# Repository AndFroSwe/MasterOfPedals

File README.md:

# Master of Pedals
A guitar pedal switching rig. Readymade presets are chosen by hitting a
footswitch on the stage pedal. The final goal of the repo is to have a modular
design that can easily be modified to the given specs.

# Features

1. At the hit of a footswitch, pedals are engaged as per the corresponding
   preset. No more tapdancing!
2. Presets can be changed on the main unit.

# Units

- __Control unit__: The main control unit. All pedals are connected to this and
presets are set here. 
- __Stage pedal__: Unit placed at the front of the stage. Has a set of
  footswitches for preset choice and a simple interface that shows the user
which preset is currently chosen.

# Repository guide

- __./Software/__ contains all source code for the MCUs. Divided into subfolders
  corresponding to the stage pedal and the control unit.
- __./KiCad/__ contains electrical schematics. Divided into subfolders
  corresponding to the stage pedal and the control unit.

# Prototype unit
The repo has a fully ready-to-go (when it's done) unit. This unit has the
following specs:

- 8 pedals in the control loop.
- 3 independently controlled amp channels.
- 6 presets.
- Stage pedal is connected via cord (i.e. it is not wireless).
- It has a simple user interface at the control unit that allows the user to
  change the presets.

# Future features
- __MIDI control output__: An output that can send MIDI messages to pedals.
- __Wireless control__: The stage pedal can send control signals to the control
  unit wirelessly. This also enables multiple control units. This could be used
in a mini control unit that is carried on the guitar.
- __Internal pedal power supply__: The control unit contains a PSU that can feed
  the guitar pedals with power.
- __Battery power supply__: The stage pedal runs on battery.
- __Data logging__: The pedal remembers which presets have been used.

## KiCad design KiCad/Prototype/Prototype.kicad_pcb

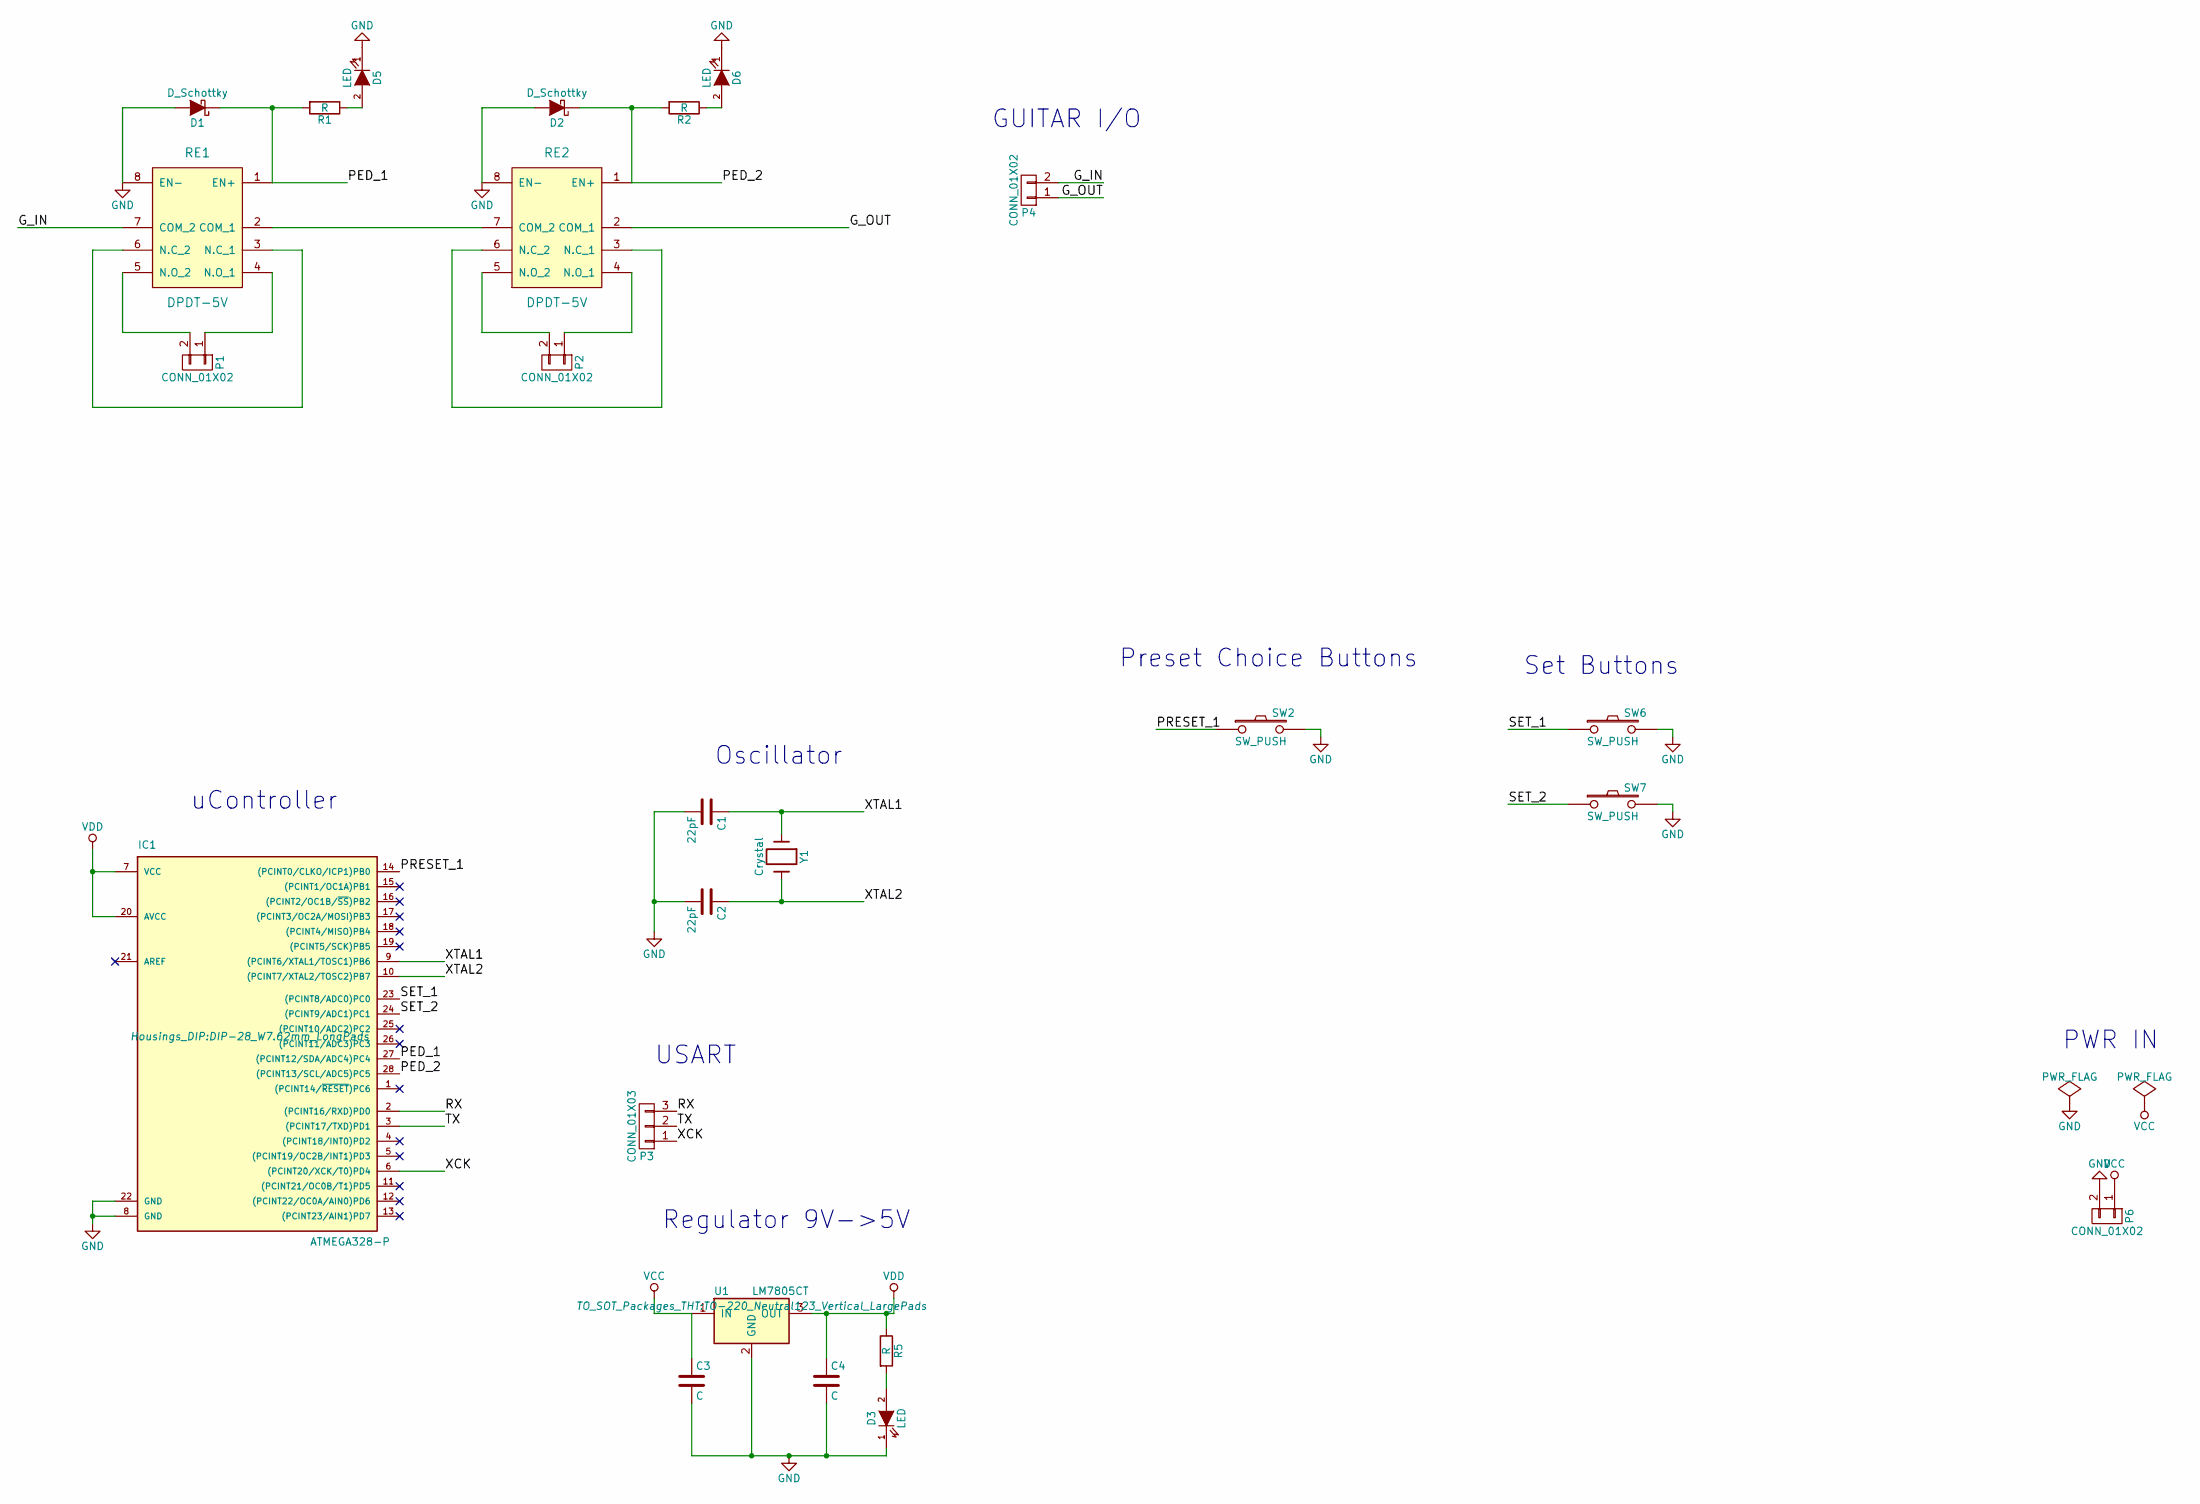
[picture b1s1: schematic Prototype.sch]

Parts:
C1, C2: 22pF; C_Disc_D3_P2.5
C3, C4: C; C_Rect_L7_W2_P5
D1, D2: D_Schottky; Diode_DO-41_SOD81_Vertical_AnodeUp
D3, D5, D6: LED; LED-5MM
IC1: ATMEGA328-P; DIP-28_W7.62mm_LongPads
P1, P2, P4, P6: CONN_01X02; Molex_KK-6410-02_02x2.54mm_Straight
P3: CONN_01X03; Molex_MicroLatch-53253-0370_03x2.00mm_Straight
R1, R2, R5: R; Resistor_Vertical_RM5mm
RE1, RE2: DPDT-5V; DS2Y_PAK
SW2, SW6, SW7: SW_PUSH; SW_PUSH_6mm
U1: LM7805CT; TO-220_Neutral123_Vertical_LargePads
Y1: Crystal; Crystal_HC49-U_Vertical

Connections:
/G_IN: P4.2, RE1.7 (COM_2)
/G_OUT: P4.1, RE2.2 (COM_1)
/PED_1: D1.1 (K), IC1.27 ((PCINT12/SDA/ADC4)PC4), R1.2, RE1.1 (EN+)
/PED_2: D2.1 (K), IC1.28 ((PCINT13/SCL/ADC5)PC5), R2.2, RE2.1 (EN+)
/PRESET_1: IC1.14 ((PCINT0/CLKO/ICP1)PB0), SW2.1
/RX: IC1.2 ((PCINT16/RXD)PD0), P3.3
/SET_1: IC1.23 ((PCINT8/ADC0)PC0), SW6.1
/SET_2: IC1.24 ((PCINT9/ADC1)PC1), SW7.1
/TX: IC1.3 ((PCINT17/TXD)PD1), P3.2
/XCK: IC1.6 ((PCINT20/XCK/T0)PD4), P3.1
/XTAL1: C1.1, IC1.9 ((PCINT6/XTAL1/TOSC1)PB6), Y1.1
/XTAL2: C2.1, IC1.10 ((PCINT7/XTAL2/TOSC2)PB7), Y1.2
GND: C1.2, C2.2, C3.2, C4.2, D1.2 (A), D2.2 (A), D3.1 (K), D5.1 (K), D6.1 (K), IC1.8 (GND), IC1.22 (GND), P6.2, RE1.8 (EN-), RE2.8 (EN-), SW2.2, SW6.2, SW7.2, U1.2 (GND); also elsewhere on the board
unnamed: D3.2 (A), R5.2
unnamed: D5.2 (A), R1.1
unnamed: D6.2 (A), R2.1
unnamed: P1.1, RE1.4 (N.O_1)
unnamed: P1.2, RE1.5 (N.O_2)
unnamed: P2.1, RE2.4 (N.O_1)
unnamed: P2.2, RE2.5 (N.O_2)
unnamed: RE1.2 (COM_1), RE2.7 (COM_2)
unnamed: RE1.3 (N.C_1), RE1.6 (N.C_2)
unnamed: RE2.3 (N.C_1), RE2.6 (N.C_2)
VCC: C3.1, P6.1, U1.1 (IN)
VDD: C4.1, IC1.7 (VCC), IC1.20 (AVCC), R5.1, U1.3 (OUT)

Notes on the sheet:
Regulator 9V->5V
uController
USART
Preset Choice Buttons
PWR IN
Oscillator
Set Buttons
GUITAR I/O

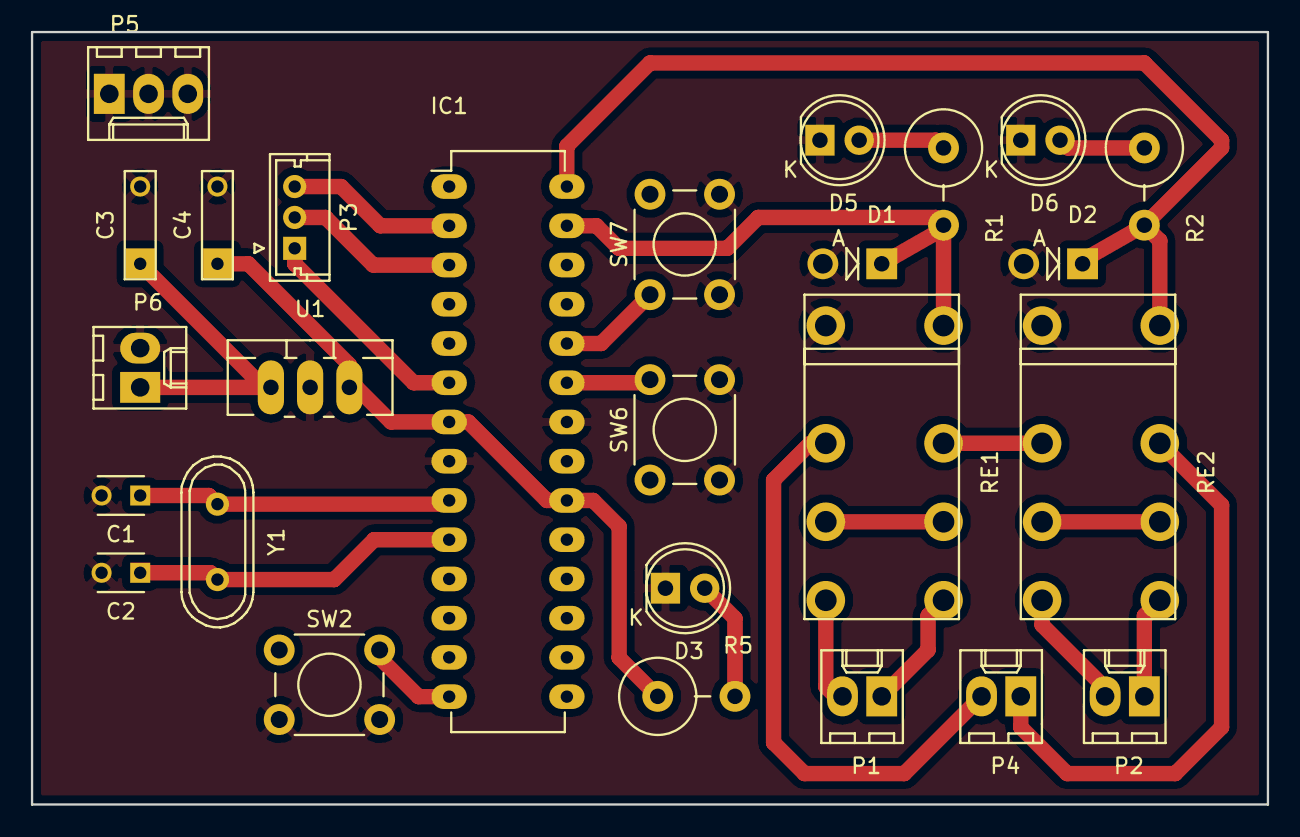
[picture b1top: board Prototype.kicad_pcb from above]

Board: 2 copper layers, 80.0 x 50.0 mm, 26 parts (0 on the bottom side), 25 nets.

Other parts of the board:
P5: CONN_01X03; Molex_KK-6410-03_03x2.54mm_Straight

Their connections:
GND: P5.1, P5.2, P5.3; also elsewhere on the board

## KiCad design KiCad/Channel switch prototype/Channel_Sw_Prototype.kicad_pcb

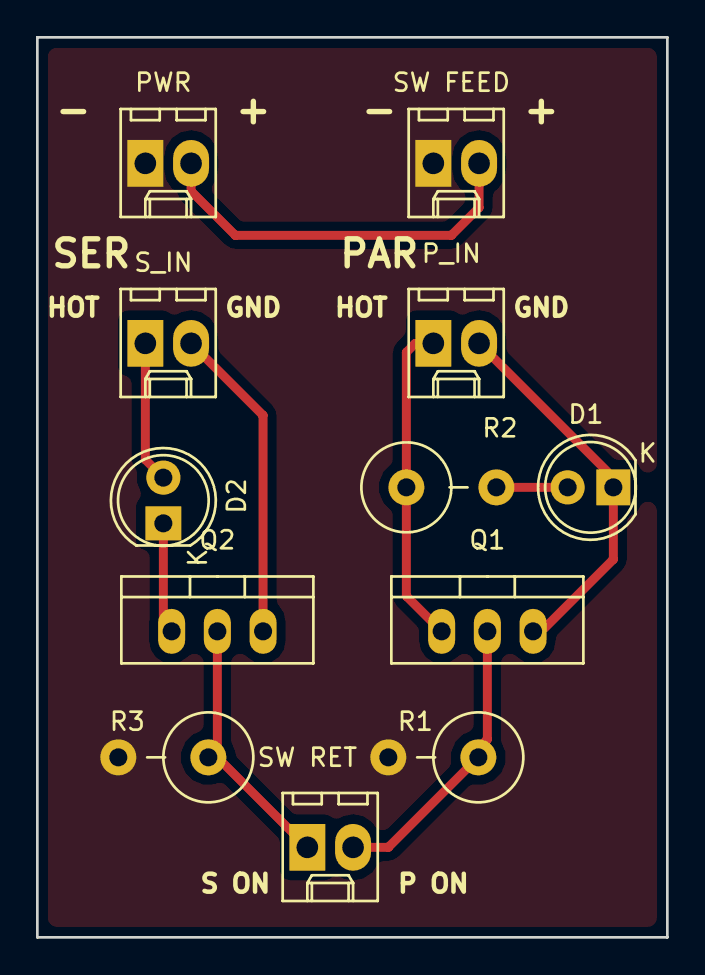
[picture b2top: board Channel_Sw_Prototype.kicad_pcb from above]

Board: 2 copper layers, 35.0 x 50.0 mm, 12 parts (0 on the bottom side), 10 nets.

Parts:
D1, D2: LED; LED-5MM
PWR: PWR; Molex_KK-6410-02_02x2.54mm_Straight
P_IN: P IN; Molex_KK-6410-02_02x2.54mm_Straight
Q1, Q2: BUZ11; TO-220_Neutral123_Vertical
R1, R3: 1M; Resistor_Vertical_RM5mm
R2: 1.5k; Resistor_Vertical_RM5mm
SW FEED: SW FEED; Molex_KK-6410-02_02x2.54mm_Straight
SW RET: SW RETURN; Molex_KK-6410-02_02x2.54mm_Straight
S_IN: S IN; Molex_KK-6410-02_02x2.54mm_Straight

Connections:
/P_ON: Q1.2, R1.1, SW RET.2
/S_ON: Q2.2, R3.1, SW RET.1
/TELE_P_GND: D1.1, P_IN.2, Q1.3
/TELE_P_HOT: P_IN.1, Q1.1, R2.1
/TELE_S_GND: Q2.3, S_IN.2
/TELE_S_HOT: D2.2, S_IN.1
GND: PWR.1, R1.2, R3.2, SW FEED.1
unnamed: D1.2, R2.2
unnamed: D2.1, Q2.1
VCC: PWR.2, SW FEED.2

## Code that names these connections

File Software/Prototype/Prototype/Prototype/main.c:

/*
 * Prototype.c
 * Simulates a small scale version of the full guitar rig. Controls two pedal switches with two
 * buttons.
 * Function:
 * - 2 pedal switching relays
 * - Two buttons for choosing preset 
 * - 1 button for customizing preset
 * - External USART connection
 *
 * Created: 11/28/2016 10:18:24 PM
 * Author : Andreas Fröderberg
 *
 * Inputs
 **************************
 * Preset_1:	PB0
 * Set_1:		PC0
 * Set_2:		PC1
 **************************
 * Outputs
 **************************
 * PED_1:		PC4
 * PED_2:		PC5
 * USART RX:	PD0
 * USART TX		PD1
 * USART XCK	PD4
 *************************
 * TODO: Button interrupt
 * TODO: USART setup
 * TODO: Preset setup function
 * TODO: Go into preset interrupt
 * TODO: Enable external crystal
 */ 

#include "main.h"

void setupInputs(void) 
{
	/* Enables input pins */
	DDRB &= ~_BV(PRESET);
	DDRC &= ~_BV(SET_1) & ~_BV(SET_2);
}

void setupOutputs(void)
{
	DDRC |= _BV(PED_1) | _BV(PED_2);
}

int main(void)
{
	setupInputs();
	setupOutputs();
	mode = 0; // Start in hot mode
	current_preset = 0;
	// Starting settings for pedals
	for (int i = 0; i < PEDALS; ++i)
	{
		pedals_hot1[i] = 1;
	}
	for (int i = 0; i < PEDALS; ++i)
	{
		pedals_hot2[i] = 0;
	}
    while (1) // Main event loop
    {
		// Read buttons
		if (!((PINB >>  SET_1) & 1)) // Set 1 is pressed
		{
			_delay_ms(DEBOUNCE_MS);
			current_preset = 1; // Toggle preset mode
		} else if (!((PINB >>  SET_2) & 1)) {// Set 2 is pressed
			_delay_ms(DEBOUNCE_MS);
			current_preset = 0; // Toggle preset mode
		}
		// Set appropriate settings
		if (current_preset == 0)
		{
			PORTC &= ~_BV(PED_1) & ~_BV(PED_2);
		} else if (current_preset == 1)
		{
			PORTC |= _BV(PED_1) | _BV(PED_2);
		}

    }
}

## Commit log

2016-06-04 Initial commit. first version of stage pedal added with prototype functions for interrupts on pedal press
2016-06-04 fixed debouncing function
2016-06-04 can now recognize which pin was triggered
2016-06-04 debouncing does not fully work, might have to change this in the future. the front pedal now has the functionality it needs
2016-06-05 basics of control pedal layed out. there is no protection for sending negative values as command now
2016-06-05 removed unnecessary prints
2016-09-30 Clean up of the repo. Added a readme and a gitignore. Made a better folder structure.
2016-09-30 Fixed spelling errors in the readme
2016-09-30 Fixed spelling errors in the readme (again)
2016-09-30 Added TODOs and a couple of more informative parts to the readme
2016-11-01 Created pedal loop and started on amp switching loop
2016-11-13 Added a future feature to the rig
2016-11-16 Added a small prototype board to test with
2016-11-18 Switched LM317 to 7805 and fixed pcb
2016-11-28 Perfected prototype and added a guitar amp switch prototype
2016-11-29 Added AVR project to prototype
2016-12-17 Added software for the prototype and made a netlist with footprints for the control unit board
2017-01-04 Added a software project for the master control unit. Encoder reading works, there is button debounce also.
2017-01-04 Made a state machine for main unit. Save or exit hierarchical state works
2017-01-10 Modified file structure. Compiles but not physically tested
2017-01-12 Fine tuned PCB design and added multicontact connectors instead of single connectors
2017-01-27 Started making a program for prototype. Preset handling done
2017-01-27 Can now read button
2017-01-27 Edited the makefile to be able to compile and flash to hw. Simple test program in main to cycle through presets
2017-01-27 Prototype works, just needs some adjustments after box is done
